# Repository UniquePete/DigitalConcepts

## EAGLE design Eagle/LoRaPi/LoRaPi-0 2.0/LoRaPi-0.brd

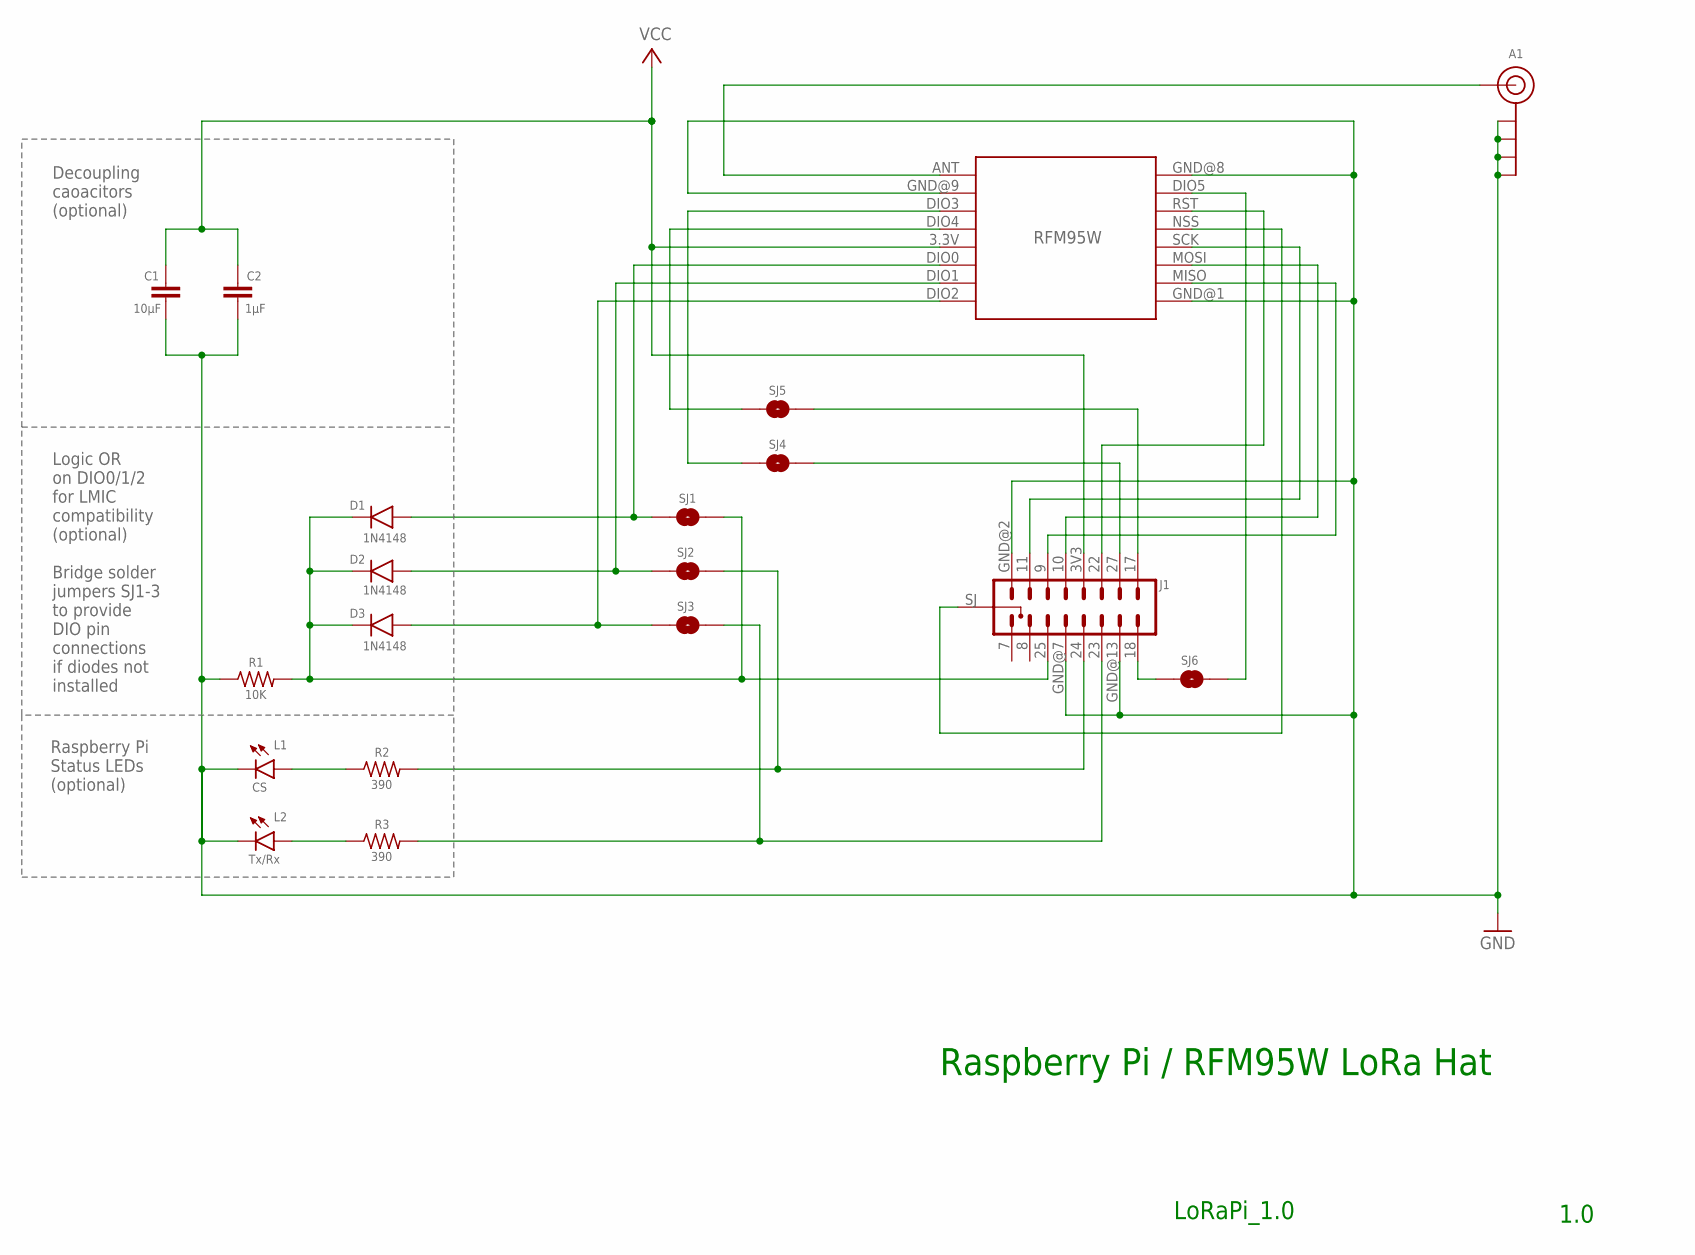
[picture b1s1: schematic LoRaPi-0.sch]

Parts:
A1: U.FL-SMA-EDGE-COMBO
C1: 10µF; C0805
C2: 1µF; C0805
D1, D2, D3: 1N4148; SOD-123
J1: HEADER-2X8-RFM95W-PI; CONN_2X8-RFM-PI
L1: CS; CHIP-LED0805
L2: Tx/Rx; CHIP-LED0805
R1: 10K; R0805
R2, R3: 390; R0805
RFM95W: RFM95W-LORA
SJ1, SJ2, SJ3, SJ4, SJ5, SJ6: SJ

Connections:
GND: A1.GND@1A (GND), A1.GND@1B (GND), A1.GND@2A (GND), A1.GND@2B (GND), C1.2, C2.2, J1.GND@2 (8), J1.GND@7 (12), J1.GND@13 (15), L1.C, L2.C, R1.1, RFM95W.GND@1 (GND.1), RFM95W.GND@8 (GND.2), RFM95W.GND@9 (GND.3)
unnamed: L2.A, R3.1
unnamed: L1.A, R2.1
unnamed: J1.18 (16), SJ6.1
unnamed: J1.SJ (8-9), RFM95W.NSS
unnamed: J1.23 (14), R3.2, SJ3.2
unnamed: J1.24 (13), R2.2, SJ2.2
unnamed: D1.2, RFM95W.DIO0, SJ1.1
unnamed: RFM95W.DIO4, SJ5.1
unnamed: RFM95W.DIO3, SJ4.1
unnamed: D1.1, D2.1, D3.1, J1.25 (11), R1.2, SJ1.2
unnamed: A1.SIG, RFM95W.ANT
unnamed: D2.2, RFM95W.DIO1, SJ2.1
unnamed: J1.22 (3), RFM95W.RST
unnamed: D3.2, RFM95W.DIO2, SJ3.1
unnamed: J1.11 (7), RFM95W.SCK
unnamed: J1.10 (5), RFM95W.MOSI
unnamed: J1.9 (6), RFM95W.MISO
unnamed: J1.27 (2), SJ4.2
unnamed: J1.17 (1), SJ5.2
unnamed: RFM95W.DIO5, SJ6.2
VCC: C1.1, C2.1, J1.3V3 (4), RFM95W.3.3V

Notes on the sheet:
1.0
Logic OR on DIO0/1/2 for LMIC compatibility (optional) Bridge solder jumpers SJ1-3 to provide DIO pin connections if diodes not installed
Raspberry Pi Status LEDs (optional)
Decoupling caoacitors (optional)
Raspberry Pi / RFM95W LoRa Hat
LoRaPi_1.0

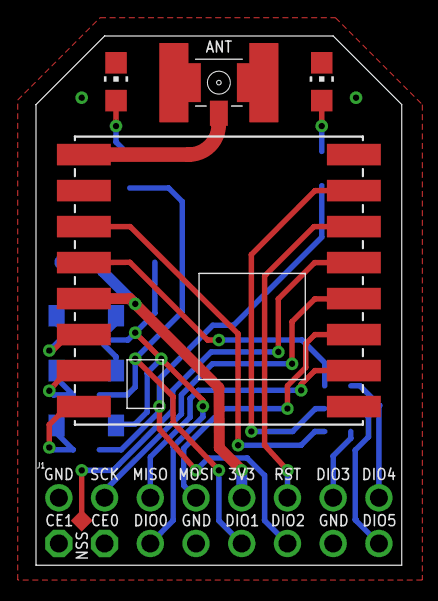
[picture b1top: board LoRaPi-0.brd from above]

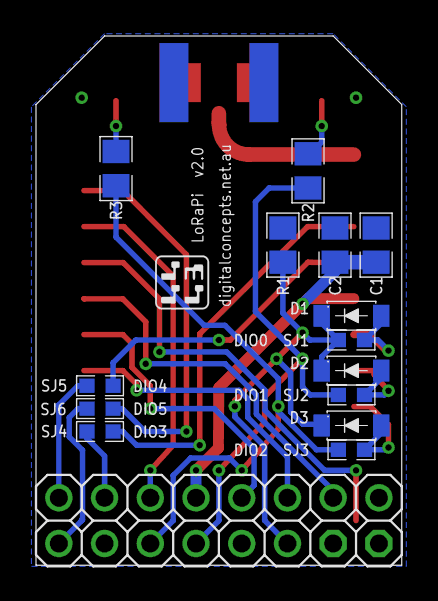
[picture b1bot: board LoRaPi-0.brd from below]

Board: 2 copper layers, 20.3 x 29.4 mm, 19 parts (14 on the bottom side), 22 nets.

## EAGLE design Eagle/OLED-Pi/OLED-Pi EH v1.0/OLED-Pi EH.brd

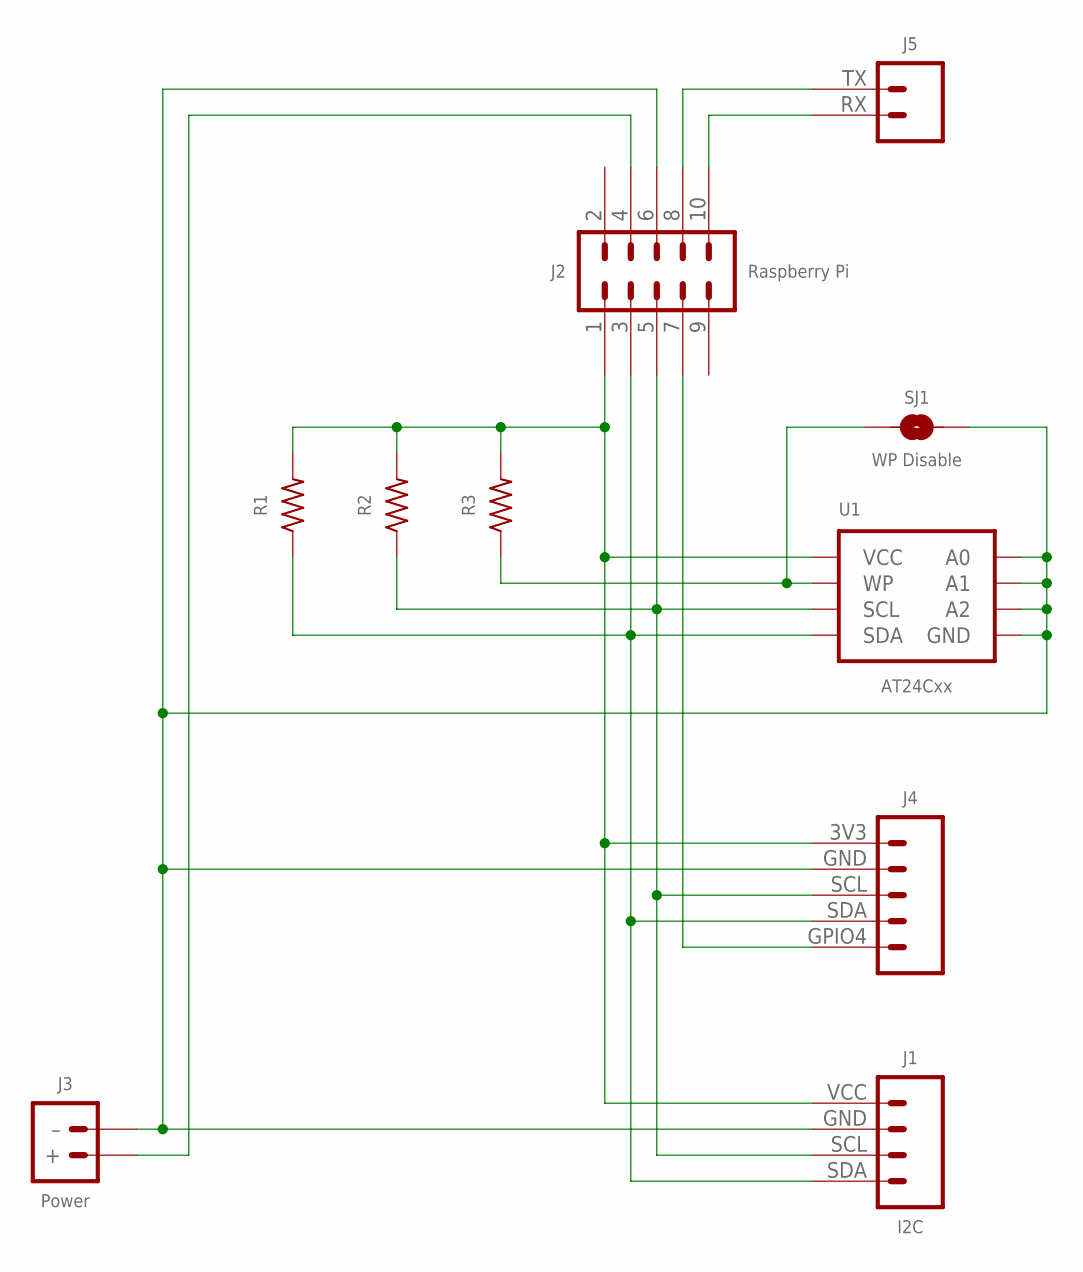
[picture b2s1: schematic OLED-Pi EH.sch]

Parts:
J1: I2C; CONN_04-I2C
J2: Raspberry Pi; CONN_2X5-PI-1
J3: Power; JST-PH2.0-2-HORIZONTAL-POWER
J4: JST-PH2.0-5-HORIZONTAL-OLED-PI
J5: JST-PH2.0-2-HORIZONTAL-TX-RXJST-PTH-2; JST-PH2.0-2-HORIZONTAL=TX-RX
R1, R2, R3: RESISTORR0805; R0805
SJ1: WP Disable; SJ
U1: AT24Cxx; SOP-8

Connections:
GND: J1.GND (2), J2.6 (8), J3.- (–), J4.GND (2), SJ1.2, U1.P$1 (A0), U1.P$2 (A1), U1.P$3 (A2), U1.P$4 (GND)
unnamed: J2.4 (9), J3.+
unnamed: J1.SDA (4), J2.3 (2), J4.SDA (4), R1.1, U1.P$5 (SDA)
unnamed: J1.SCL (3), J2.5 (3), J4.SCL (3), R2.1, U1.P$6 (SCL)
unnamed: J2.7 (4), J4.GPIO4 (5)
unnamed: J2.10 (6), J5.RX (2)
unnamed: J2.8 (7), J5.TX (1)
unnamed: R3.1, SJ1.1, U1.P$7 (WP)
VCC: J1.VCC (1), J2.1, J4.3V3 (1), R1.2, R2.2, R3.2, U1.P$8 (VCC)

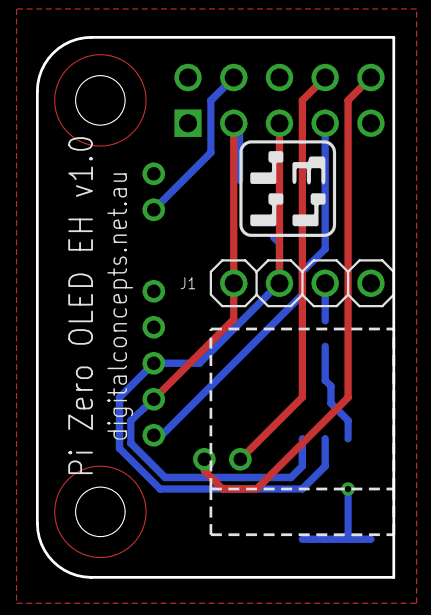
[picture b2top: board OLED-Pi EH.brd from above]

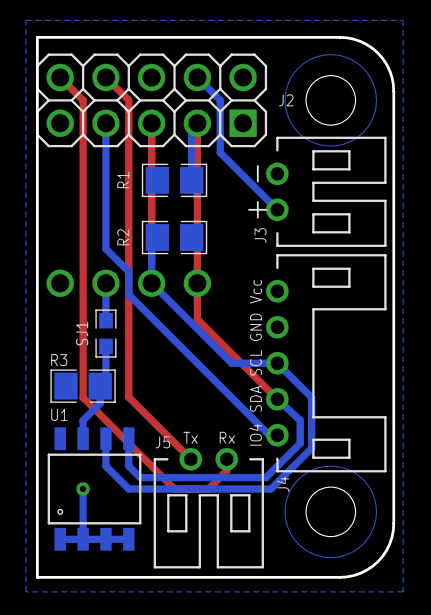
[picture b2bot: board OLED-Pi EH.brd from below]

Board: 2 copper layers, 19.8 x 30.0 mm, 10 parts (8 on the bottom side), 9 nets.

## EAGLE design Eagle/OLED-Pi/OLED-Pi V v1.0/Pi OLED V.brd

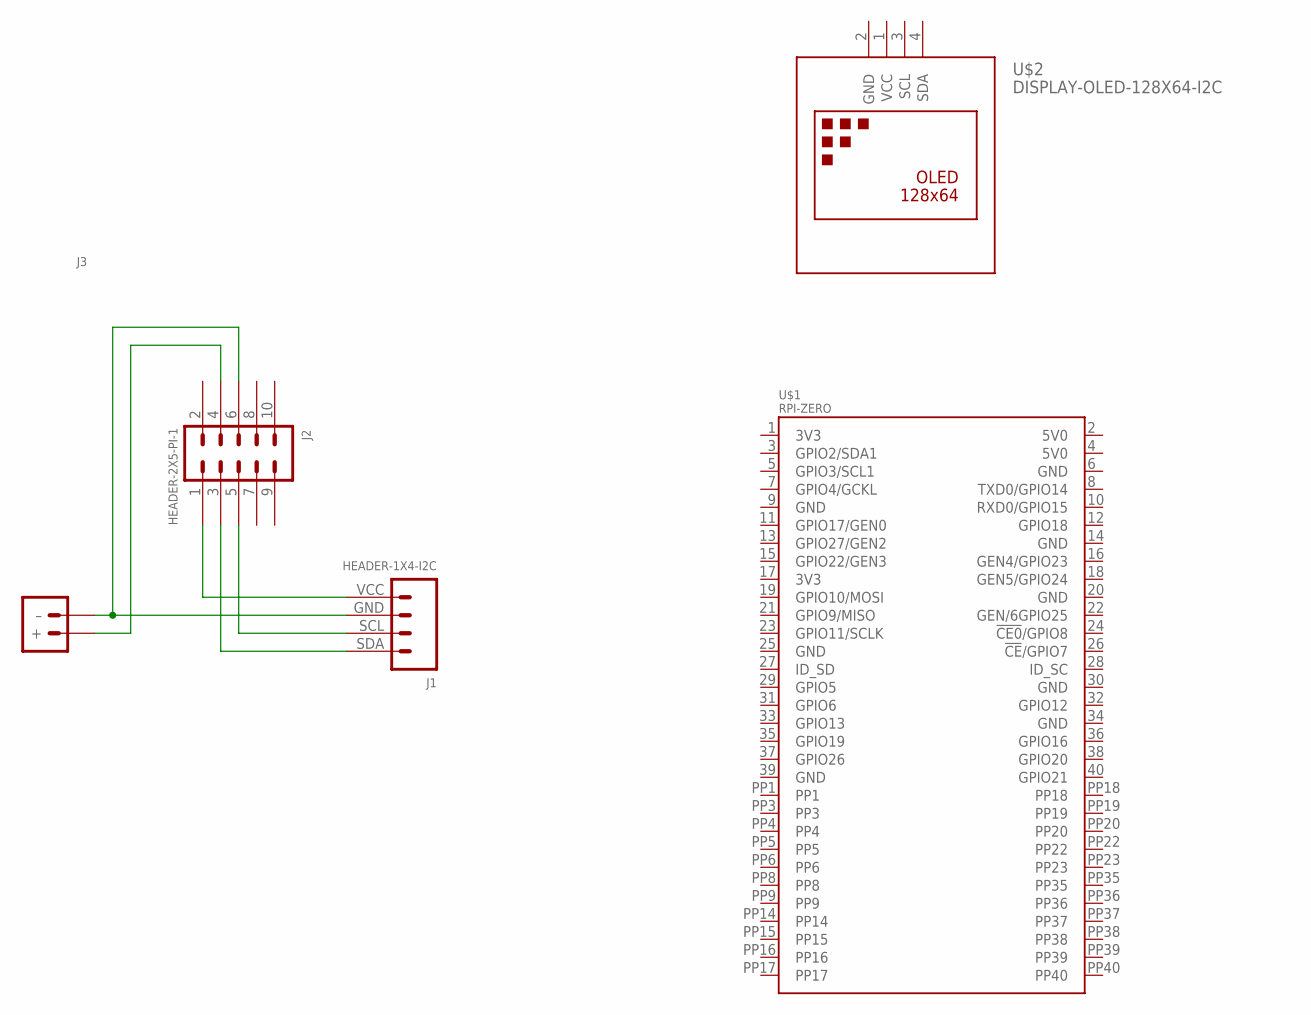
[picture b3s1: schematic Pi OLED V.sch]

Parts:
J1: HEADER-1X4-I2C; CONN_04-I2C
J2: HEADER-2X5-PI-1; CONN_2X5-PI-1
J3: JST-PH2.0-2-HORIZONTAL-POWERJST-PTH-2; JST-PH2.0-2-HORIZONTAL-POWER
U$1: RPI-ZERO; RASP_PI_ZERO_BOARD_FULL
U$2: DISPLAY-OLED-128X64-I2C

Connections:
GND: U$2.2 (GND)
unnamed: J1.GND (2), J2.6 (8), J3.- (–)
unnamed: J2.4 (9), J3.+
unnamed: J1.VCC (1), J2.1
unnamed: J1.SDA (4), J2.3 (2)
unnamed: J1.SCL (3), J2.5 (3)
VCC: U$2.1 (VCC)

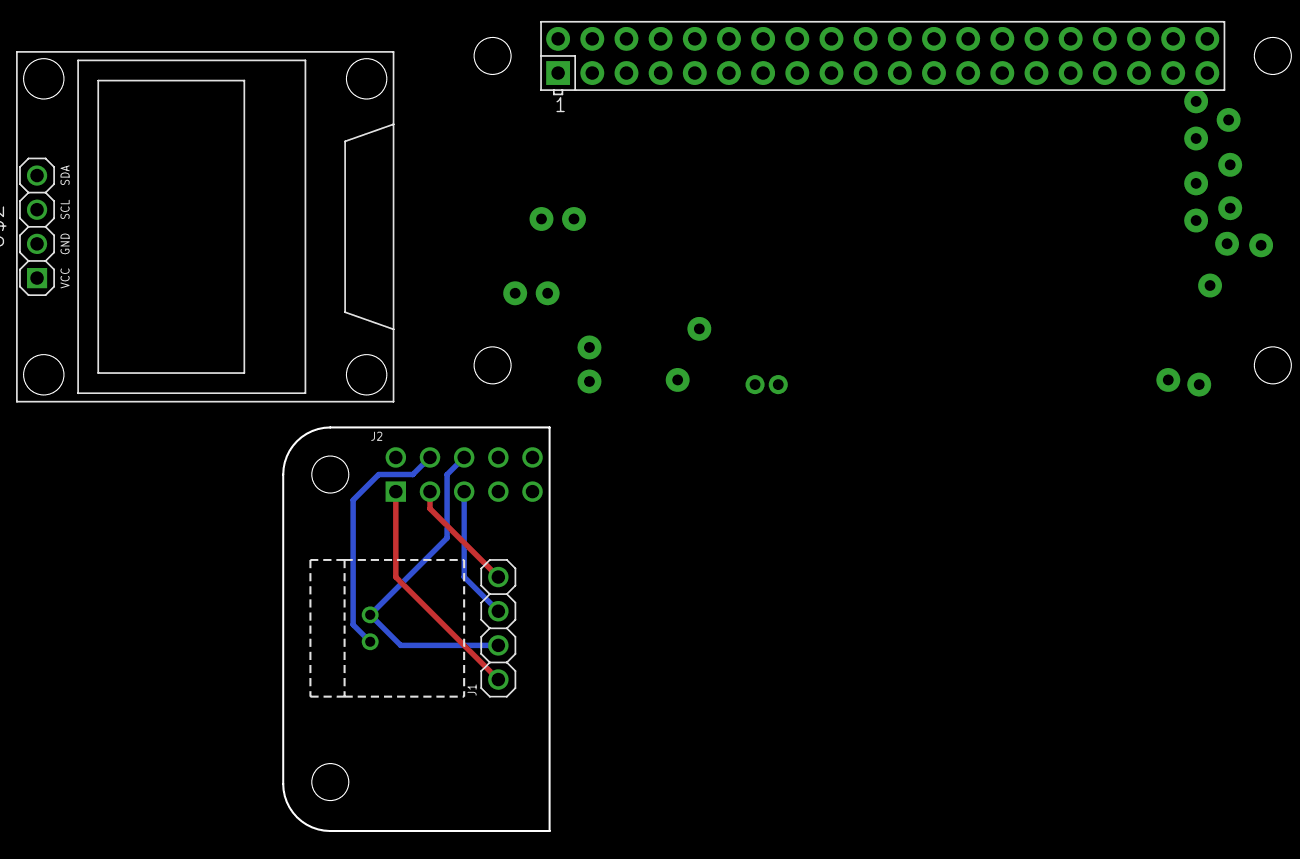
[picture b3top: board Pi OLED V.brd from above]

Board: 2 copper layers, 19.8 x 30.0 mm, 5 parts (1 on the bottom side), 5 nets.

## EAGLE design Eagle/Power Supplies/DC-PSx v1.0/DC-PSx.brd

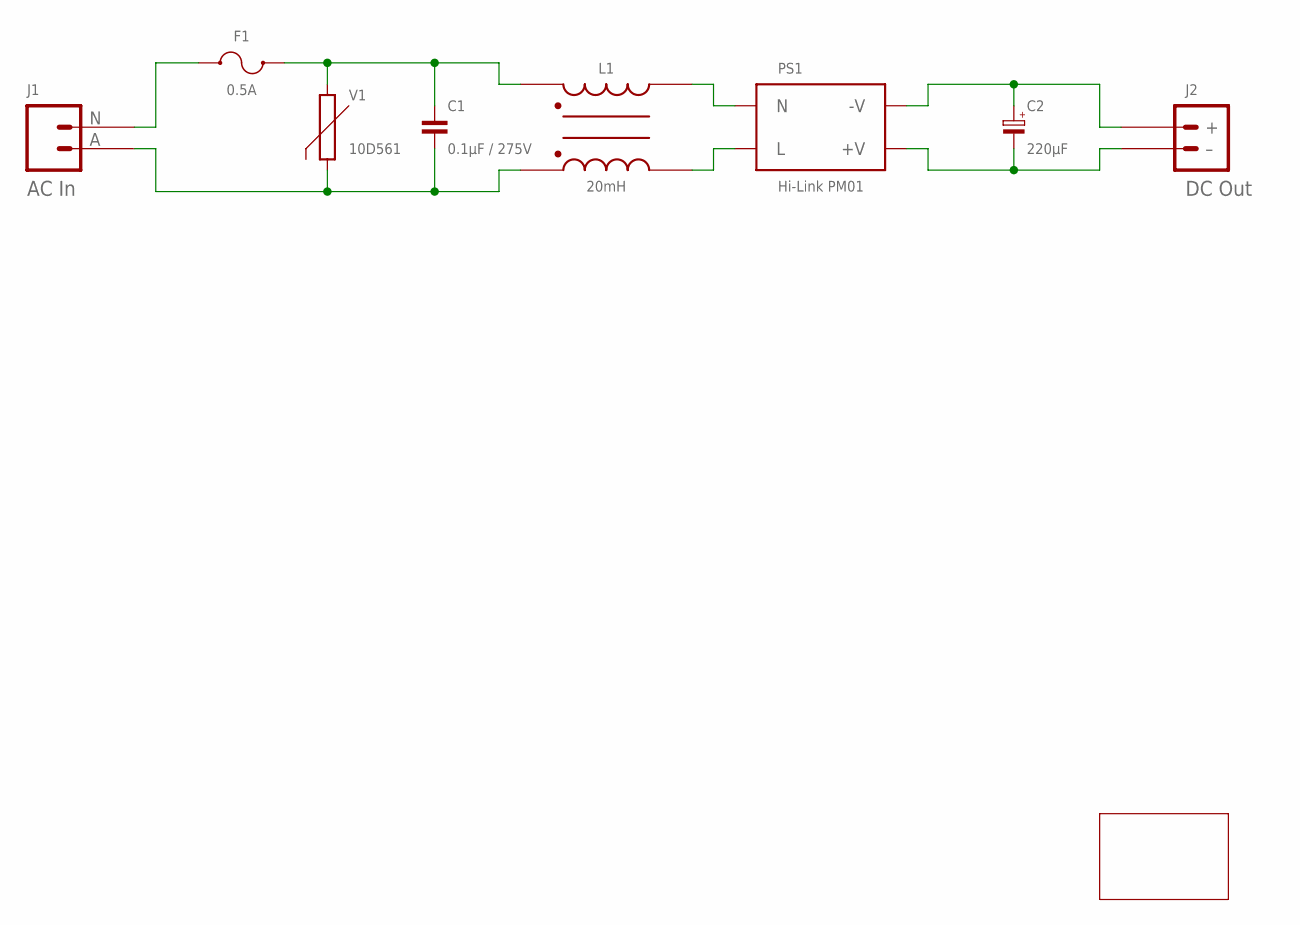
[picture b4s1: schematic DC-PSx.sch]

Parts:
C1: 0.1µF / 275V; CAPACITOR-TENTA-SUPPRESSION
C2: 220µF; E5-10,5
F1: 0.5A; FUSE-HOLDER-1808
J1: AC In; DB-03_AC_POWER_SOCKET
J2: DC Out; JST-PH2.0-2-VERTICAL-POWER
L1: 20mH; INDUCTOR-UU9.8
PCB1: PCB-OUTLINE-64X36; PCB-POWER-SUPPLY-3
PS1: Hi-Link PM01; HI-LINK_PM0X
V1: 10D561; VARISTOR-10D561

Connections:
unnamed: F1.P$1 (1), J1.N (1)
unnamed: C1.P$1 (1), F1.P$2 (2), L1.P$1 (1), V1.2
unnamed: L1.P$2 (2), PS1.AC-N (N)
unnamed: C1.P$2 (2), J1.A (2), L1.P$4 (4), V1.1
unnamed: L1.P$3 (3), PS1.AC-L (L)
unnamed: C2.+, J2.+, PS1.-VO (-V)
unnamed: C2.-, J2.- (–), PS1.+VO (+V)

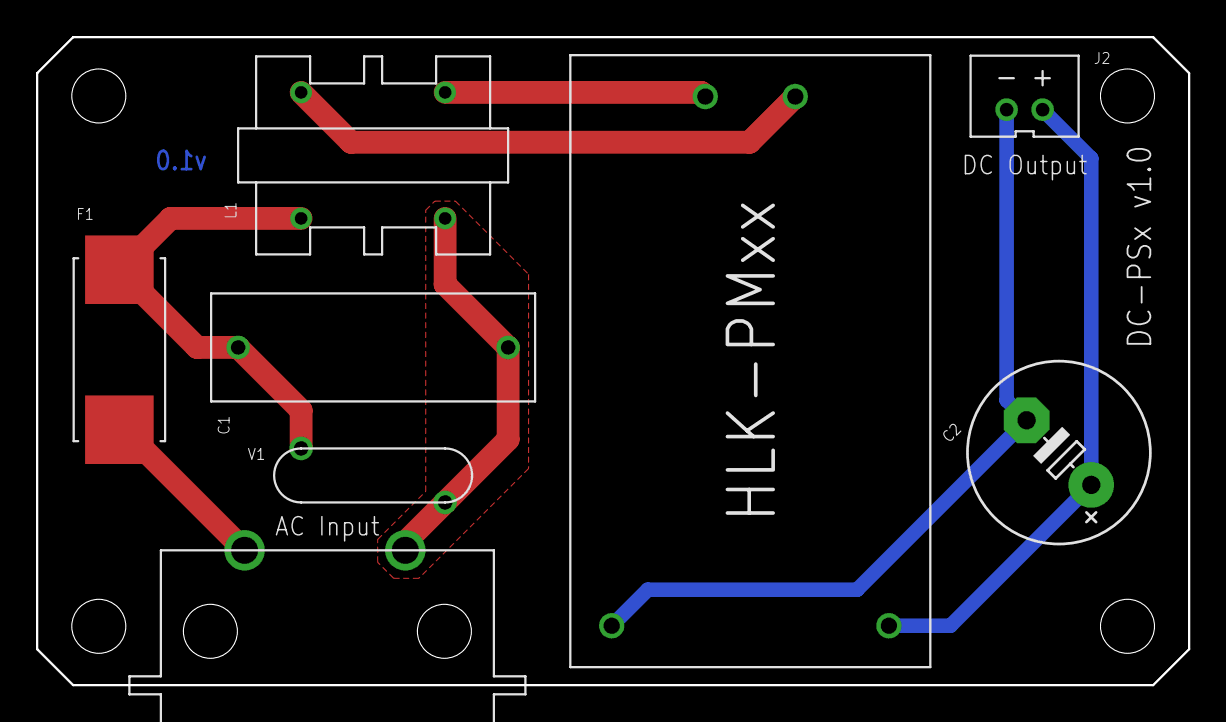
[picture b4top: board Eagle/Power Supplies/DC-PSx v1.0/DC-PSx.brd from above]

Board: 2 copper layers, 64.0 x 36.0 mm, 9 parts (0 on the bottom side), 7 nets.

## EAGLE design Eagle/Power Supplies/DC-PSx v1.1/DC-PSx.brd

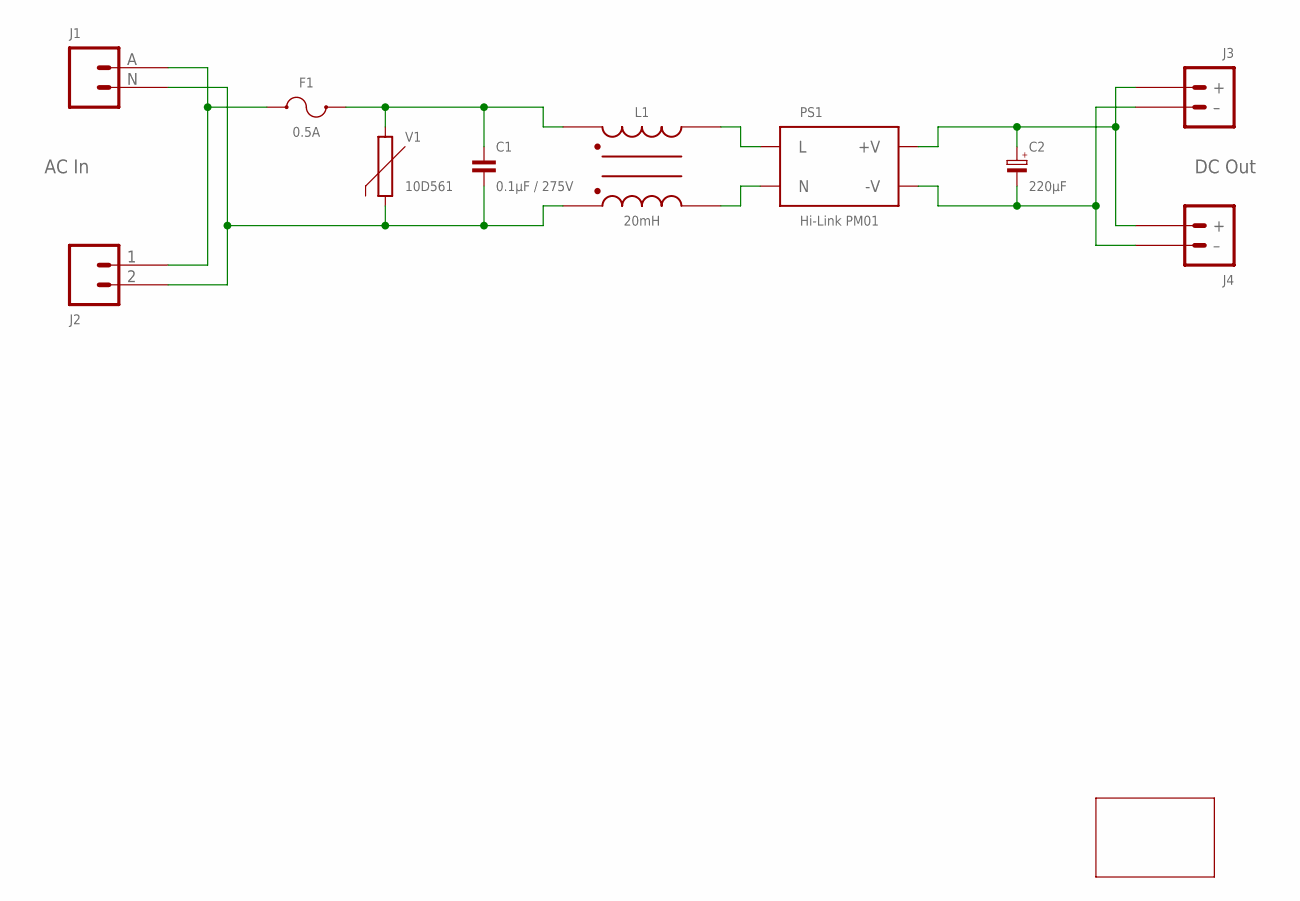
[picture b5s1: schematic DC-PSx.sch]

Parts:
C1: 0.1µF / 275V; CAPACITOR-TENTA-SUPPRESSION
C2: 220µF; E5-10,5
F1: 0.5A; FUSE-HOLDER-1808
J1: AC In; DB-03_AC_POWER_SOCKET
J2: TERMINAL_SCREW_2P_VERTICAL; TERMINAL-SCREW-2P
J3: DC Out; JST-PH2.0-2-VERTICAL-POWER
J4: TERMINAL_SCREW_2P_POWER; TERMINAL-SCREW-2P
L1: 20mH; INDUCTOR-UU9.8
PCB1: PCB-OUTLINE-64X36; PCB-POWER-SUPPLY-3
PS1: Hi-Link PM01; HI-LINK_PM0X
V1: 10D561; VARISTOR-10D561

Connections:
unnamed: F1.P$1 (1), J1.A (2), J2.1
unnamed: C1.P$1 (1), F1.P$2 (2), L1.P$1 (1), V1.2
unnamed: L1.P$2 (2), PS1.AC-L (L)
unnamed: C1.P$2 (2), J1.N (1), J2.2, L1.P$4 (4), V1.1
unnamed: L1.P$3 (3), PS1.AC-N (N)
unnamed: C2.+, J3.+, J4.2 (+), PS1.+VO (+V)
unnamed: C2.-, J3.- (–), J4.1 (–), PS1.-VO (-V)

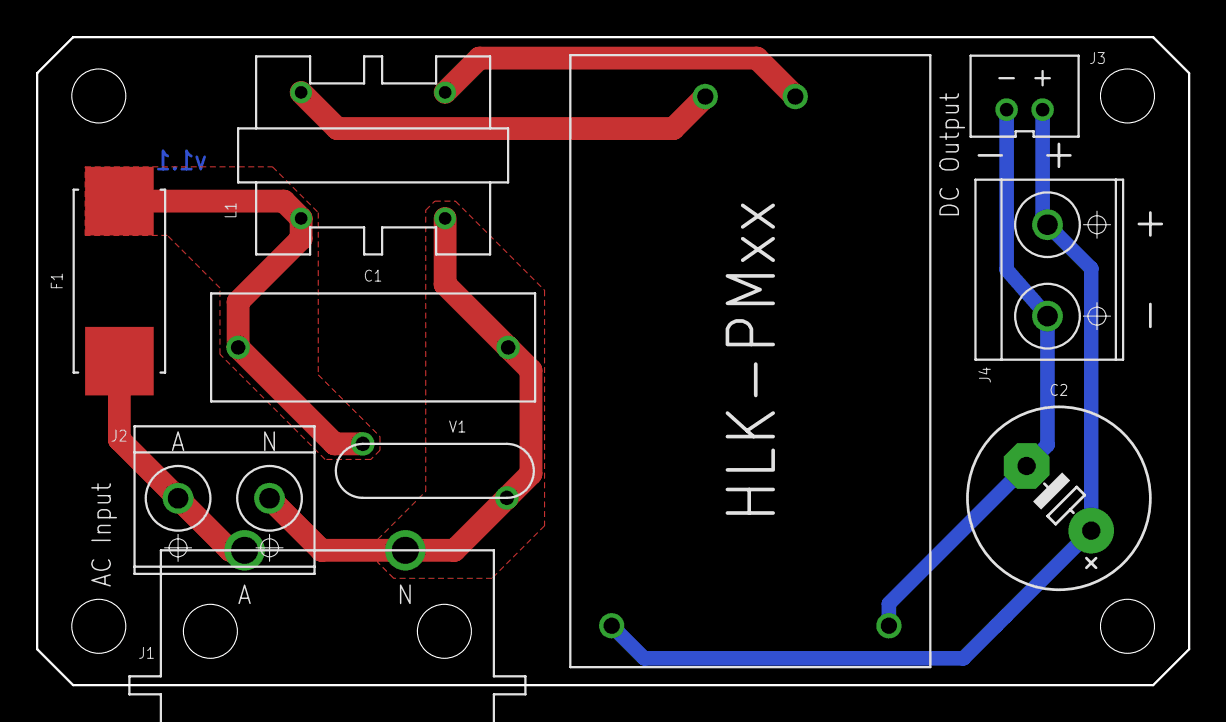
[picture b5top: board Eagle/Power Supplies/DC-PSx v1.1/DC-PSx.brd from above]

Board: 2 copper layers, 64.0 x 36.0 mm, 11 parts (0 on the bottom side), 7 nets.
